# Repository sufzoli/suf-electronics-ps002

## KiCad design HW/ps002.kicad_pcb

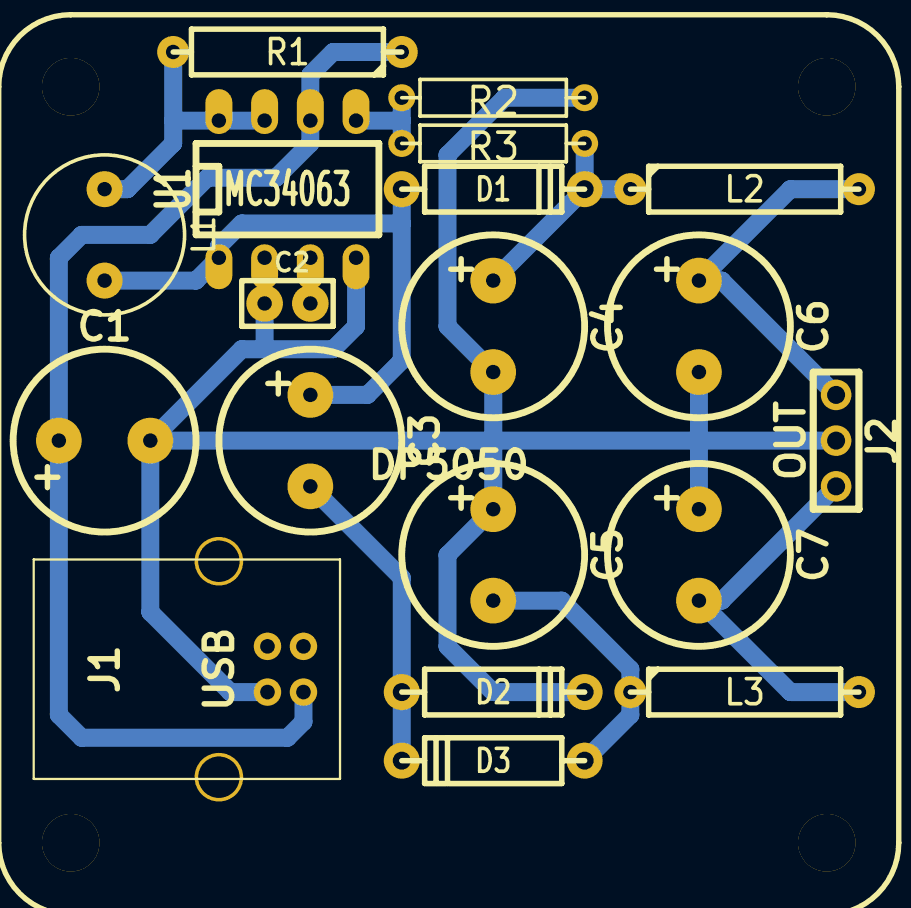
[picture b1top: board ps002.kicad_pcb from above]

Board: 2 copper layers, 20 parts (0 on the bottom side), 11 nets.

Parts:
C1: 470uF/10V; C2P_D4
C2: 330pF; C1
C3, C4, C5: 470uF/25V; C2P_D4
C6, C7: 470uF/16V; C2P_D4
D1, D2, D3: 1N5819; D4
DP5050: DP5050
J1: USB; USB_B
J2: OUT; HDR-3
L1: 100uH; L2_D3.5
L2, L3: 1uH; R5
R1: R47/1W; R5
R2: 1K5; R4
R3: 13K; R4
U1: MC34063; DIP-8

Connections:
GND: C1.2, C2.1, C4.2, C5.1, C6.2, C7.1, D2.2, J1.4, J2.2, R2.2, U1.2, U1.4
unnamed: R2.1, R3.1, U1.5
unnamed: C3.2, D2.1, D3.2
unnamed: C3.1, D1.1, L1.2, U1.1
unnamed: C2.2, U1.3
unnamed: C7.2, J2.3, L3.2
unnamed: C6.1, J2.1, L2.2
unnamed: C5.2, D3.1, L3.1
unnamed: C4.1, D1.2, L2.1, R3.2
unnamed: L1.1, R1.2, U1.7, U1.8
VCC: C1.1, J1.1, R1.1, U1.6

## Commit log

2014-09-17 schematic design added
2014-09-18 Schematic diagram completted PCB design started
2014-09-18 PCB Routed
2014-10-11 PS002 B version added Separate controllers for positive and negative sides
2021-03-20 Update cache
